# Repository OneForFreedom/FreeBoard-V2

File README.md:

# FreeBoard-V2
I made this because I want this to be my every day keyboard! I chose colours I like, and made it how I like it. 
This is a FULL iso layout keyboard (105 keys) and has a rot enc for volumne control!

# Mouth watering images (Ik youre salavating):

# BOM
| Item                | Price (£) | Price (\$) | Link                                                          |
| ------------------- | --------- | ---------- | ------------------------------------------------------------- |
| Stab Lube           | 1.52      | 2.05       | [Link](https://www.aliexpress.com/item/1005008432501049.html) |
| Keycaps             | 7.41      | 10.00      | [Link](https://www.aliexpress.com/item/1005006922735195.html) |
| Stabilisers (Stabs) | 6.39      | 8.63       | [Link](https://www.aliexpress.com/item/32719735398.html)      |
| Copper Wick         | 1.25      | 1.69       | [Link](https://www.aliexpress.com/item/1005007589879020.html) |
| Grip Tape           | 2.66      | 3.59       | [Link](https://www.aliexpress.com/item/1005008164935173.html) |
| Super Glue          | 2.75      | 3.71       | [Link](https://www.aliexpress.com/item/1005008583356354.html) |
| Hex Nuts            | 0.82      | 1.11       | [Link](https://www.aliexpress.com/item/4000602853448.html)    |
| Switches (x5)       | 2.55      | 3.44       | [Link](https://www.aliexpress.com/item/1005006578935785.html) |
| Diodes (x4)         | 2.84      | 3.83       | [Link](https://www.aliexpress.com/item/1005006245109375.html) |
| Rubber O-Rings      | 0.58      | 0.78       | [Link](https://www.aliexpress.com/item/32965363255.html)      |
| Switch Pads         | 2.54      | 3.43       | [Link](https://www.aliexpress.com/item/1005006454684461.html) |
| Rotary Encoders     | 1.90      | 2.57       | [Link](https://www.aliexpress.com/item/1005005983134515.html) |
| Flux                | 4.09      | 5.52       | [Link](https://www.aliexpress.com/item/1005006588523672.html) |
| Switch Film         | 2.01      | 2.71       | [Link](https://www.aliexpress.com/item/1005006584258877.html) |
| Hex Screws          | 7.44      | 10.04      | [Link](https://www.aliexpress.com/item/1005004833667162.html) |
| Rotary Encoder Caps | 1.06      | 1.43       | [Link](https://www.aliexpress.com/item/1005005983134515.html) |
| Raspberry Pi Pico   | 2.08      | 2.81       | [Link](https://www.aliexpress.com/item/1005008513003531.html) |
| USB Cable (Micro)   | 0.93      | 1.26       | [Link](https://www.aliexpress.com/item/1005007138392516.html) |
| Felt Pads (to mount pcb)   | N/A      | N/A       | N/A |
| JLCPCB PCB          | 46.27     | 62.46      | [Link](https://www.jlcpcb.com)    |
| Royal Mail Shipping | 3.35      | 4.52       | [Link](https://www.royalmail.com) |

| Currency | Amount   |
| -------- | -------- |
| Pounds   | £111.65  |
| Dollars  | \$150.72 |
 
 (ONE DOLLAR DISCOUNT MAKES THIS $149.72)

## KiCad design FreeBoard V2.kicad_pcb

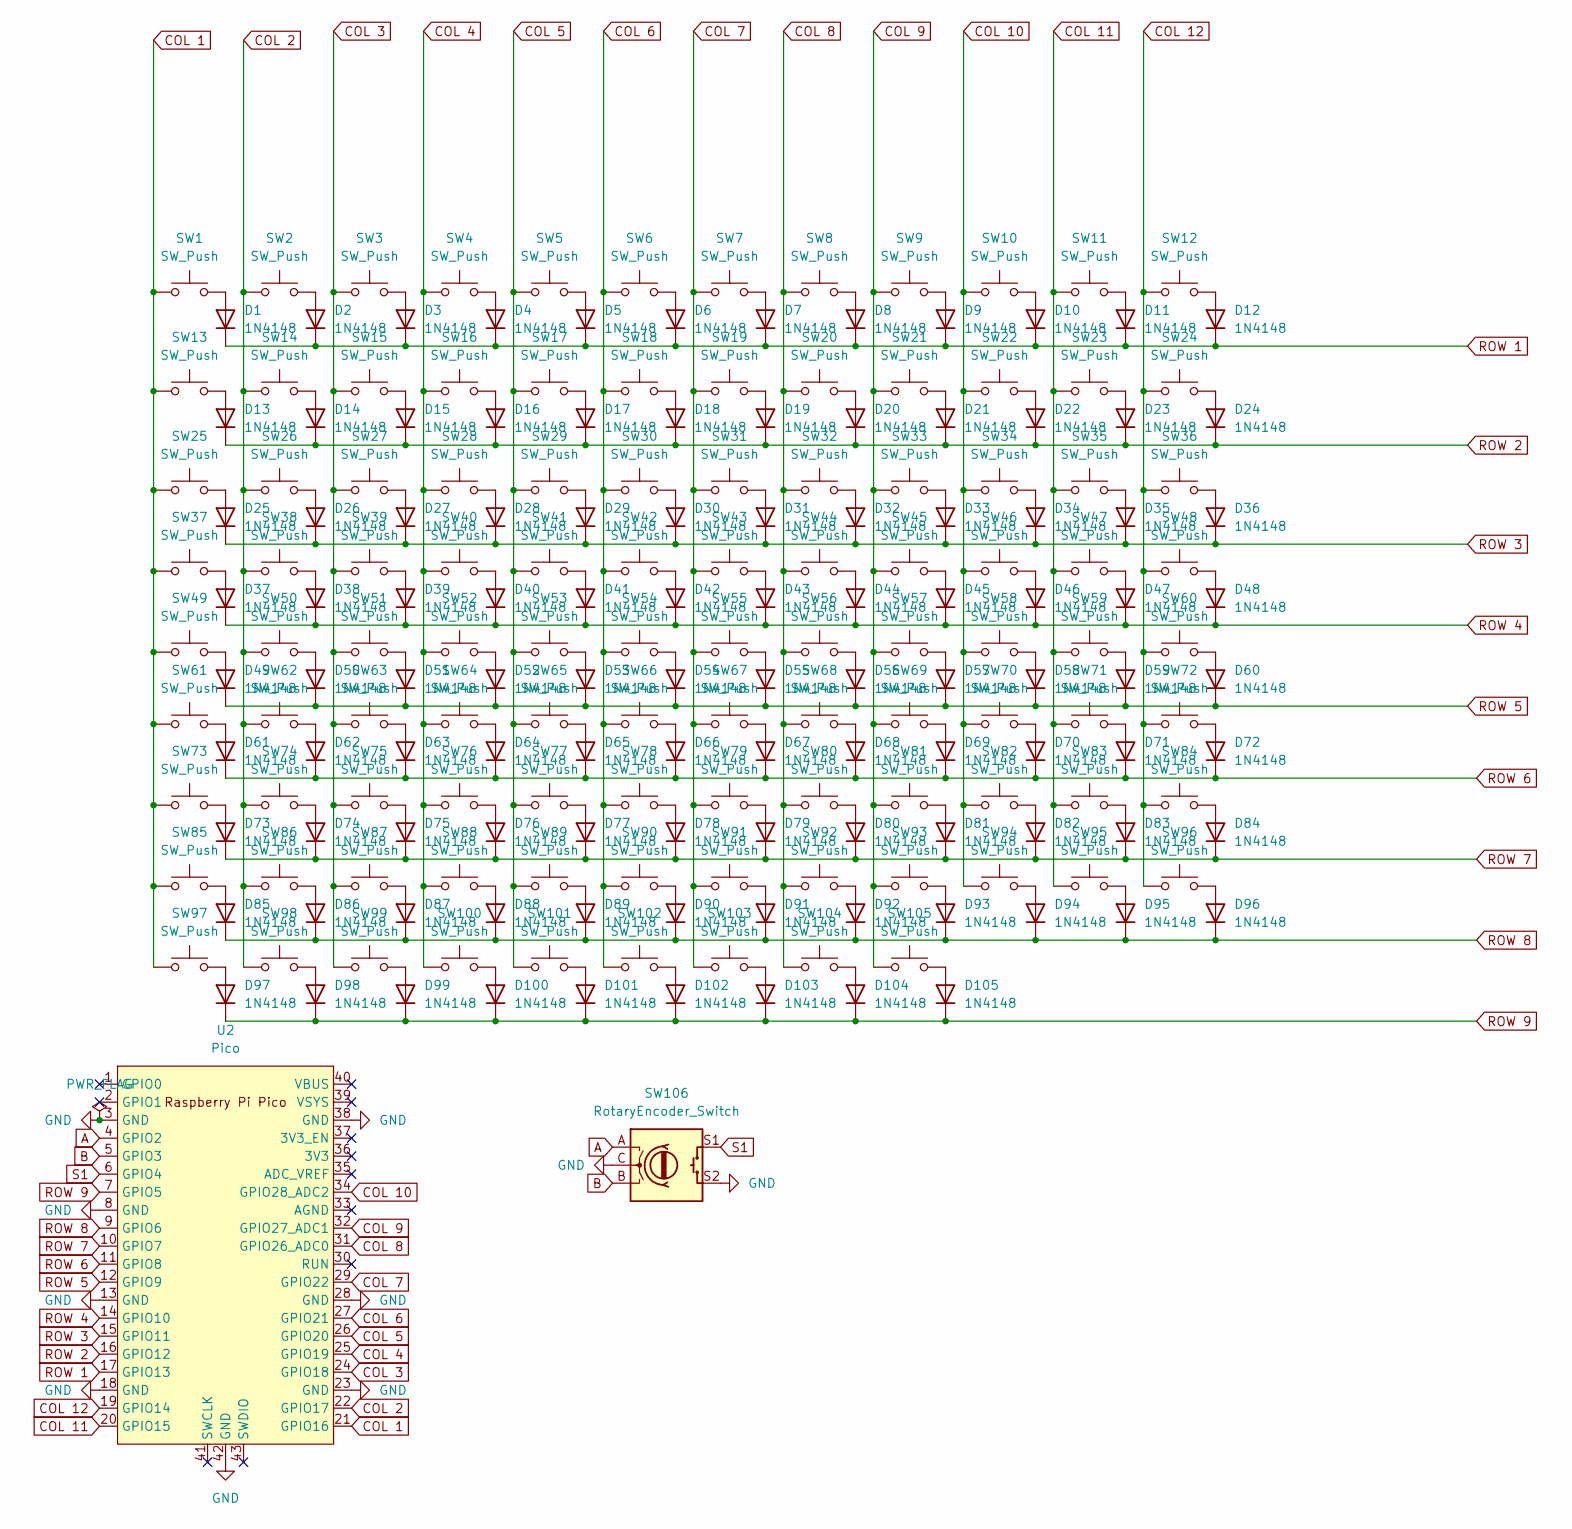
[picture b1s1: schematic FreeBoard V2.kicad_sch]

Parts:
D1, D2, D3, D4, D5, D6, D7, D8, D9, D10, D11, D12, D13, D14, D15, D16, D17, D18, D19, D20, D21, D22, D23, D24, D25, D26, D27, D28, D29, D30, D31, D32, D33, D34, D35, D36, D37, D38, D39, D40, D41, D42, D43, D44, D45, D46, D47, D48, D49, D50, D51, D52, D53, D54, D55, D56, D57, D58, D59, D60, D61, D62, D63, D64, D65, D66, D67, D68, D69, D70, D71, D72, D73, D74, D75, D76, D77, D78, D79, D80, D81, D82, D83, D84, D85, D86, D87, D88, D89, D90, D91, D92, D93, D94, D95, D96, D97, D98, D99, D100, D101, D102, D103, D104, D105: 1N4148; D_DO-35_SOD27_P7.62mm_Horizontal
SW1, SW2, SW3, SW4, SW5, SW6, SW7, SW8, SW9, SW10, SW11, SW12, SW13, SW14, SW15, SW16, SW17, SW18, SW19, SW20, SW21, SW22, SW23, SW24, SW25, SW26, SW27, SW28, SW29, SW30, SW31, SW32, SW33, SW34, SW35, SW36, SW37, SW38, SW39, SW40, SW41, SW42, SW43, SW44, SW45, SW46, SW47, SW48, SW49, SW50, SW51, SW52, SW53, SW54, SW55, SW56, SW57, SW58, SW59, SW60, SW61, SW62, SW63, SW64, SW65, SW66, SW67, SW68, SW69, SW70, SW71, SW72, SW73, SW74, SW75, SW76, SW77, SW78, SW79, SW80, SW81, SW82, SW83, SW84, SW85, SW86, SW87, SW88, SW89, SW90, SW91, SW92, SW93, SW94, SW95, SW96, SW97, SW98, SW99, SW100, SW101, SW102, SW103, SW104, SW105: SW_Push; SW_Cherry_MX_1.00u_PCB
SW106: RotaryEncoder_Switch; RotaryEncoder_Alps_EC11E-Switch_Vertical_H20mm_MountingHoles
U2: Pico; RPi_Pico_SMD_TH

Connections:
A: SW106.A, U2.4 (GPIO2)
B: SW106.B, U2.5 (GPIO3)
COL 1: SW1.1, SW13.1, SW25.1, SW37.1, SW49.1, SW61.1, SW73.1, SW85.1, SW97.1, U2.21 (GPIO16)
COL 2: SW2.1, SW14.1, SW26.1, SW38.1, SW50.1, SW62.1, SW74.1, SW86.1, SW98.1, U2.22 (GPIO17)
COL 3: SW3.1, SW15.1, SW27.1, SW39.1, SW51.1, SW63.1, SW75.1, SW87.1, SW99.1, U2.24 (GPIO18)
COL 4: SW4.1, SW16.1, SW28.1, SW40.1, SW52.1, SW64.1, SW76.1, SW88.1, SW100.1, U2.25 (GPIO19)
COL 5: SW5.1, SW17.1, SW29.1, SW41.1, SW53.1, SW65.1, SW77.1, SW89.1, SW101.1, U2.26 (GPIO20)
COL 6: SW6.1, SW18.1, SW30.1, SW42.1, SW54.1, SW66.1, SW78.1, SW90.1, SW102.1, U2.27 (GPIO21)
COL 7: SW7.1, SW19.1, SW31.1, SW43.1, SW55.1, SW67.1, SW79.1, SW91.1, SW103.1, U2.29 (GPIO22)
COL 8: SW8.1, SW20.1, SW32.1, SW44.1, SW56.1, SW68.1, SW80.1, SW92.1, SW104.1, U2.31 (GPIO26_ADC0)
COL 9: SW9.1, SW21.1, SW33.1, SW45.1, SW57.1, SW69.1, SW81.1, SW93.1, SW105.1, U2.32 (GPIO27_ADC1)
COL 10: SW10.1, SW22.1, SW34.1, SW46.1, SW58.1, SW70.1, SW82.1, SW94.1, U2.34 (GPIO28_ADC2)
COL 11: SW11.1, SW23.1, SW35.1, SW47.1, SW59.1, SW71.1, SW83.1, SW95.1, U2.20 (GPIO15)
COL 12: SW12.1, SW24.1, SW36.1, SW48.1, SW60.1, SW72.1, SW84.1, SW96.1, U2.19 (GPIO14)
GND: SW106.C, SW106.S2, U2.3 (GND), U2.8 (GND), U2.13 (GND), U2.18 (GND), U2.23 (GND), U2.28 (GND), U2.38 (GND), U2.42 (GND)
unnamed: D1.2 (A), SW1.2
unnamed: D2.2 (A), SW2.2
unnamed: D3.2 (A), SW3.2
unnamed: D4.2 (A), SW4.2
unnamed: D5.2 (A), SW5.2
unnamed: D6.2 (A), SW6.2
unnamed: D7.2 (A), SW7.2
unnamed: D8.2 (A), SW8.2
unnamed: D9.2 (A), SW9.2
unnamed: D10.2 (A), SW10.2
unnamed: D11.2 (A), SW11.2
unnamed: D12.2 (A), SW12.2
unnamed: D13.2 (A), SW13.2
unnamed: D14.2 (A), SW14.2
unnamed: D15.2 (A), SW15.2
unnamed: D16.2 (A), SW16.2
unnamed: D17.2 (A), SW17.2
unnamed: D18.2 (A), SW18.2
unnamed: D19.2 (A), SW19.2
unnamed: D20.2 (A), SW20.2
unnamed: D21.2 (A), SW21.2
unnamed: D22.2 (A), SW22.2
unnamed: D23.2 (A), SW23.2
unnamed: D24.2 (A), SW24.2
unnamed: D25.2 (A), SW25.2
unnamed: D26.2 (A), SW26.2
unnamed: D27.2 (A), SW27.2
unnamed: D28.2 (A), SW28.2
unnamed: D29.2 (A), SW29.2
unnamed: D30.2 (A), SW30.2
unnamed: D31.2 (A), SW31.2
unnamed: D32.2 (A), SW32.2
unnamed: D33.2 (A), SW33.2
unnamed: D34.2 (A), SW34.2
unnamed: D35.2 (A), SW35.2
unnamed: D36.2 (A), SW36.2
unnamed: D37.2 (A), SW37.2
unnamed: D38.2 (A), SW38.2
unnamed: D39.2 (A), SW39.2
unnamed: D40.2 (A), SW40.2
unnamed: D41.2 (A), SW41.2
unnamed: D42.2 (A), SW42.2
unnamed: D43.2 (A), SW43.2
unnamed: D44.2 (A), SW44.2
unnamed: D45.2 (A), SW45.2
unnamed: D46.2 (A), SW46.2
unnamed: D47.2 (A), SW47.2
unnamed: D48.2 (A), SW48.2
unnamed: D49.2 (A), SW49.2
unnamed: D50.2 (A), SW50.2
unnamed: D51.2 (A), SW51.2
unnamed: D52.2 (A), SW52.2
unnamed: D53.2 (A), SW53.2
unnamed: D54.2 (A), SW54.2
unnamed: D55.2 (A), SW55.2
unnamed: D56.2 (A), SW56.2
unnamed: D57.2 (A), SW57.2
unnamed: D58.2 (A), SW58.2
unnamed: D59.2 (A), SW59.2
unnamed: D60.2 (A), SW60.2
unnamed: D61.2 (A), SW61.2
unnamed: D62.2 (A), SW62.2
unnamed: D63.2 (A), SW63.2
unnamed: D64.2 (A), SW64.2
unnamed: D65.2 (A), SW65.2
unnamed: D66.2 (A), SW66.2
unnamed: D67.2 (A), SW67.2
unnamed: D68.2 (A), SW68.2
unnamed: D69.2 (A), SW69.2
unnamed: D70.2 (A), SW70.2
unnamed: D71.2 (A), SW71.2
unnamed: D72.2 (A), SW72.2
unnamed: D73.2 (A), SW73.2
unnamed: D74.2 (A), SW74.2
unnamed: D75.2 (A), SW75.2
unnamed: D76.2 (A), SW76.2
unnamed: D77.2 (A), SW77.2
unnamed: D78.2 (A), SW78.2
unnamed: D79.2 (A), SW79.2
unnamed: D80.2 (A), SW80.2
unnamed: D81.2 (A), SW81.2
unnamed: D82.2 (A), SW82.2
unnamed: D83.2 (A), SW83.2
unnamed: D84.2 (A), SW84.2
unnamed: D85.2 (A), SW85.2
unnamed: D86.2 (A), SW86.2
unnamed: D87.2 (A), SW87.2
unnamed: D88.2 (A), SW88.2
unnamed: D89.2 (A), SW89.2
unnamed: D90.2 (A), SW90.2
unnamed: D91.2 (A), SW91.2
unnamed: D92.2 (A), SW92.2
unnamed: D93.2 (A), SW93.2
unnamed: D94.2 (A), SW94.2
unnamed: D95.2 (A), SW95.2
unnamed: D96.2 (A), SW96.2
unnamed: D97.2 (A), SW97.2
unnamed: D98.2 (A), SW98.2
unnamed: D99.2 (A), SW99.2
unnamed: D100.2 (A), SW100.2
unnamed: D101.2 (A), SW101.2
unnamed: D102.2 (A), SW102.2
unnamed: D103.2 (A), SW103.2
unnamed: D104.2 (A), SW104.2
unnamed: D105.2 (A), SW105.2
ROW 1: D1.1 (K), D2.1 (K), D3.1 (K), D4.1 (K), D5.1 (K), D6.1 (K), D7.1 (K), D8.1 (K), D9.1 (K), D10.1 (K), D11.1 (K), D12.1 (K), U2.17 (GPIO13)
ROW 2: D13.1 (K), D14.1 (K), D15.1 (K), D16.1 (K), D17.1 (K), D18.1 (K), D19.1 (K), D20.1 (K), D21.1 (K), D22.1 (K), D23.1 (K), D24.1 (K), U2.16 (GPIO12)
ROW 3: D25.1 (K), D26.1 (K), D27.1 (K), D28.1 (K), D29.1 (K), D30.1 (K), D31.1 (K), D32.1 (K), D33.1 (K), D34.1 (K), D35.1 (K), D36.1 (K), U2.15 (GPIO11)
ROW 4: D37.1 (K), D38.1 (K), D39.1 (K), D40.1 (K), D41.1 (K), D42.1 (K), D43.1 (K), D44.1 (K), D45.1 (K), D46.1 (K), D47.1 (K), D48.1 (K), U2.14 (GPIO10)
ROW 5: D49.1 (K), D50.1 (K), D51.1 (K), D52.1 (K), D53.1 (K), D54.1 (K), D55.1 (K), D56.1 (K), D57.1 (K), D58.1 (K), D59.1 (K), D60.1 (K), U2.12 (GPIO9)
ROW 6: D61.1 (K), D62.1 (K), D63.1 (K), D64.1 (K), D65.1 (K), D66.1 (K), D67.1 (K), D68.1 (K), D69.1 (K), D70.1 (K), D71.1 (K), D72.1 (K), U2.11 (GPIO8)
ROW 7: D73.1 (K), D74.1 (K), D75.1 (K), D76.1 (K), D77.1 (K), D78.1 (K), D79.1 (K), D80.1 (K), D81.1 (K), D82.1 (K), D83.1 (K), D84.1 (K), U2.10 (GPIO7)
ROW 8: D85.1 (K), D86.1 (K), D87.1 (K), D88.1 (K), D89.1 (K), D90.1 (K), D91.1 (K), D92.1 (K), D93.1 (K), D94.1 (K), D95.1 (K), D96.1 (K), U2.9 (GPIO6)
ROW 9: D97.1 (K), D98.1 (K), D99.1 (K), D100.1 (K), D101.1 (K), D102.1 (K), D103.1 (K), D104.1 (K), D105.1 (K), U2.7 (GPIO5)
S1: SW106.S1, U2.6 (GPIO4)

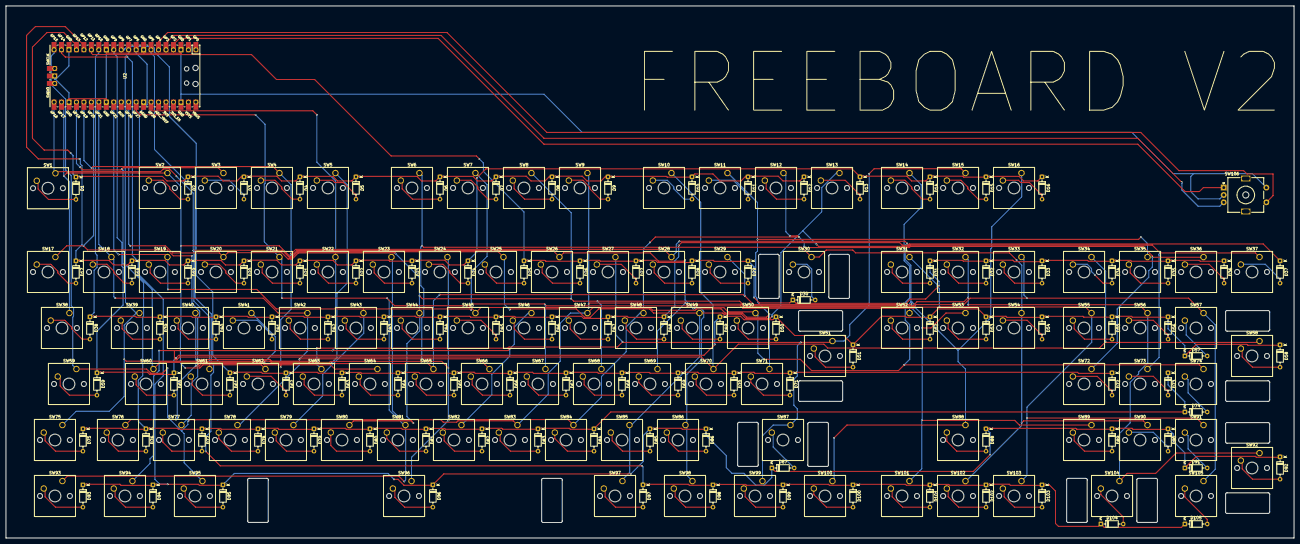
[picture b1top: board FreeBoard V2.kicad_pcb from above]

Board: 2 copper layers, 438.2 x 181.0 mm, 212 parts (0 on the bottom side), 130 nets.

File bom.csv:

Designator,Footprint,Quantity,Value,LCSC Part #
"D1, D10, D100, D101, D102, D103, D104, D105, D11, D12, D13, D14, D15, D16, D17, D18, D19, D2, D20, D21, D22, D23, D24, D25, D26, D27, D28, D29, D3, D30, D31, D32, D33, D34, D35, D36, D37, D38, D39, D4, D40, D41, D42, D43, D44, D45, D46, D47, D48, D49, D5, D50, D51, D52, D53, D54, D55, D56, D57, D58, D59, D6, D60, D61, D62, D63, D64, D65, D66, D67, D68, D69, D7, D70, D71, D72, D73, D74, D75, D76, D77, D78, D79, D8, D80, D81, D82, D83, D84, D85, D86, D87, D88, D89, D9, D90, D91, D92, D93, D94, D95, D96, D97, D98, D99",D_DO-35_SOD27_P7.62mm_Horizontal,105,1N4148,
"SW1, SW10, SW100, SW101, SW102, SW103, SW104, SW105, SW11, SW12, SW13, SW14, SW15, SW16, SW17, SW18, SW19, SW2, SW20, SW21, SW22, SW23, SW24, SW25, SW26, SW27, SW28, SW29, SW3, SW30, SW31, SW32, SW33, SW34, SW35, SW36, SW37, SW38, SW39, SW4, SW40, SW41, SW42, SW43, SW44, SW45, SW46, SW47, SW48, SW49, SW5, SW50, SW51, SW52, SW53, SW54, SW55, SW56, SW57, SW58, SW59, SW6, SW60, SW61, SW62, SW63, SW64, SW65, SW66, SW67, SW68, SW69, SW7, SW70, SW71, SW72, SW73, SW74, SW75, SW76, SW77, SW78, SW79, SW8, SW80, SW81, SW82, SW83, SW84, SW85, SW86, SW87, SW88, SW89, SW9, SW90, SW91, SW92, SW93, SW94, SW95, SW96, SW97, SW98, SW99",SW_Cherry_MX_1.00u_PCB,105,SW_Push,
SW106,RotaryEncoder_Alps_EC11E-Switch_Vertical_H20mm_MountingHoles,1,RotaryEncoder_Switch,
U2,RPi_Pico_SMD_TH,1,Pico,

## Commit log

2025-07-13 Rename FreeBoard_V2.zip to Production/FreeBoard_V2.zip
2025-07-13 Rename FreeBoard V2.kicad_prl to KiCad/FreeBoard V2.kicad_prl
2025-07-13 Rename FreeBoard V2.kicad_pro to KiCad/FreeBoard V2.kicad_pro
2025-07-13 Rename FreeBoard V2.step to Cad/FreeBoard V2.step
2025-07-13 Create 2342
